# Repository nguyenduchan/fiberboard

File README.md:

# Fiberboard

Fiberboard là bo mạch điều khiển **logic tích hợp (AIO)**, không có driver stepper Nema. Dùng cho bơm DC, cấp liệu feeder, báo vật thể lạ và mini filler.

Trên bo có **đế cắm ESP32-DevKitC** (nạp phần mềm nhúng qua USB trên module). Nguồn vào **9–24 VDC**. Hai kênh quang **sợi POF 1 mm** (AFBR) gắn trên PCB. Đầu ra relay và van solenoid, **RS485**. Mỗi giắc vào/ra có **đèn SMD 0805** sát cọc. Trong cột nguồn có đèn debug: **D27** sáng khi +24 V sau bảo vệ còn điện, **D25** khi buck ra +5 V, **D6** khi LDO ra 3,3 V. Không có header OLED trên bo.

Kho mã này chỉ chứa thiết kế KiCad và script sinh mạch/layout. **Phần mềm nhúng (firmware)** không có trong kho.

Ghi chú thiết kế chi tiết: [`pcb/DESIGN_NOTES.txt`](pcb/DESIGN_NOTES.txt)

Khối **bảo vệ 24 V + buck** (dùng chung nhiều loại bo): [`pcb/PWR_24V_PROTECT_BUCK_GUIDE.txt`](pcb/PWR_24V_PROTECT_BUCK_GUIDE.txt)

---

## Chức năng các khối

| Khối | Mô tả |
|------|--------|
| **MCU** | ESP32-DevKitC trên đế cắm; nạp firmware qua USB trên module |
| **Nguồn** | VIN → **F1/L2/RV1/D7/Q12/C4** → **XL1509** → **+5V**. Mỗi relay lấy +5 V qua ferrite riêng (FB4 / FB5). **AMS1117** → 3,3 V. Chỉ **một** cầu chì F1 tại nguồn tổng 24 V. Mass **NT1+D11+C23+FB3**. Chi tiết: [`pcb/PWR_24V_PROTECT_BUCK_GUIDE.txt`](pcb/PWR_24V_PROTECT_BUCK_GUIDE.txt) |
| **Quang 2 kênh** | Phát AFBR-1624Z + thu AFBR-2624Z mỗi kênh; sợi POF 1 mm cắm trên bo |
| **Đầu vào số** | FOOT (công tắc chân), NPN (cảm biến); cách ly quang PC817 |
| **Đầu ra** | 2 relay G6KU (COM/NO/NC) + 1 van solenoid (MOSFET 24 V); domino J5/J6/J7 (**2EDG5.08**, bước 5,08 mm); flyback D3/D4 (cuộn relay 5 V), D5 SS34 (solenoid trên J7); driver 2N3904 + AO3400A. Tiếp điểm relay kín — tải cảm lớn: snubber/diode tại tải hoặc theo catalog relay |
| **Giao tiếp** | RS485 bán song công (MAX485); **TVS D9/D10** + **R18/R19** trên A/B; LED trạng thái; I2C chỉ trên ESP32 |

Bảo vệ trên bo (tóm tắt): **F1** = đế cầu chì **5×20 mm có nắp** (chân 22,6 mm) tại nguồn tổng 24 V, ống sứ 4 A thay bằng tay, không PPTC SMD; **L2, RV1, D7, C4**; mass **NT1, D11, C23, FB3**; relay **D12/C24**; van lấy **+24V** sau F1. Đèn **Vào / Chì / 24V / 5V / 3V3** chỉ chỗ nguồn đứt. Đầu vào quang PC817; RS485 **D9/D10**. Lắp tủ: nguồn 24 V ≥ 1,5–2 A, dây xoắn, IEC 61000-6-2; dừng khẩn / SIL — phần cứng an toàn riêng.

---

## Đầu nối ra ngoài (I/O)

**Cạnh dài trên** (trái → phải): `J1 | J3 | J4 | F1T | F1R | F2T | F2R` — nguồn vào 24 V, chân, NPN, quang.

**Cạnh dài dưới** (trái → phải): `J5 | J6 | J7 | J2 | J8` — relay 1, relay 2, van, giắc 24 V ra cho bàn phím, rồi RS485. Các giắc giãn trên suốt cạnh; cột relay, van và RS485 rộng hơn để xếp linh kiện trong khung của cọc. Cột trái trong lòng là bảo vệ 24 V, cột kế là buck.

| Ref | Tên | Chân | Ý nghĩa |
|-----|-----|------|---------|
| **J1** | VIN | 1 | +9 … +24 VDC |
| | | 2 | Mass domino nguồn |
| **F1T** | Quang 1 phát | POF | Phát; cắm sợi 1 mm thẳng vào mắt hướng ra cạnh bo |
| **F1R** | Quang 1 thu | POF | Thu kênh 1 (cùng chiều cắm như phát) |
| **F2T** | Quang 2 phát | POF | Phát kênh 2 |
| **F2R** | Quang 2 thu | POF | Thu kênh 2 |
| **J3** | FOOT | 1 | Cực A công tắc chân (qua opto) |
| | | 2 | Cực K / mass về |
| **J4** | NPN | 1 | V+ 24 V cho cảm biến hiện trường |
| | | 2 | SIG (tín hiệu NPN) |
| | | 3 | Mass hiện trường (GND_PWR) |
| **J5** | RELAY 1 | 1 / 2 / 3 | COM / NO / NC |
| **J6** | RELAY 2 | 1 / 2 / 3 | COM / NO / NC |
| **J7** | SOLENOID | 1 | +24 V (cực dương cuộn van) |
| | | 2 | SOL− (cực âm; bo cắt mass phía âm) |
| **J2** | Keyboard | 1 / 2 | +24 V đã qua F1 (cùng rail +24V) / mass nguồn. Cấp cho J_PWR mạch keyboard |
| **J8** | RS485 | 1 / 2 / 3 | A / B / mass logic (**2EDG5.08-3P** cái trên bo) |

### Domino hiện trường — **2EDG5.08** (dễ mua Shopee)

| Hạng mục | Khuyến nghị |
|----------|-------------|
| **Trên PCB** | Socket **2EDG5.08** cái, chân ngang 5,08 mm (footprint `Fiberboard:Terminal_2EDG5.08-…`) |
| **Dây ra hiện trường** | **Đầu đực 2EDG** cùng bước (bộ **đực + cái** 2P/3P), siết dây vào đực; hoặc cáp **CH5.08** một đầu + đầu đực 2EDG tùy shop |
| **Tìm mua** | Shopee: `2EDG5.08 3P đực cái thẳng` · `2EDG5.08 2P` · `cáp CH5.08 3P 20cm` (đầu jack — thường gắn thêm đực 2EDG nếu cần) |

### RS485 (J8)

| Hạng mục | Khuyến nghị |
|----------|-------------|
| **Cắm** | **2EDG5.08-3P** đực (giống J4–J6) |
| **Cáp** | Đôi xoắn **2×0,25–0,5 mm²** + bọc chắn; **A/B** chân 1–2, **mass** chân 3; bọc chắn nối mass **một đầu** |
| **Trên bo** | **R15 100 Ω** giữa A–B (điểm cuối bus — termination; gộp mã với R13) |
| **Bố trí** | **J8** ở **cạnh dài dưới** (cùng hàng relay/van), góc phải |

| Ref | Socket trên bo | Dây hiện trường (phổ biến VN) |
|-----|----------------|-------------------------------|
| **J1, J3, J7** | 2EDG **2P** cái | Đực **2EDG5.08-2P** + dây 0,5–1,5 mm² |
| **J4, J5, J6, J8** | 2EDG **3P** cái | Đực **2EDG5.08-3P** (+ cáp xoắn có bọc cho RS485) |

Cột I/O tính theo **bề ngang cắm đực 2EDG**, xếp trên **cạnh dài** của hộp 145×90×40.

---

## GPIO ESP32 (tham chiếu firmware)

Tên tín hiệu trong firmware giữ nguyên; cột **Hướng** = vào/ra MCU.

| GPIO | Tín hiệu | Hướng | Ghi chú |
|------|-----------|-------|---------|
| IO32 | FIBER1_PWM | Ra | LEDC PWM → phát quang kênh 1 |
| IO33 | FIBER2_PWM | Ra | LEDC PWM → phát quang kênh 2 |
| IO4 | FIBER1_DIG | Vào | TTL từ thu quang kênh 1 |
| IO15 | FIBER2_DIG | Vào | TTL từ thu quang kênh 2 |
| IO25 | IN_FOOT | Vào | Công tắc chân (sau opto) |
| IO26 | IN_NPN | Vào | Cảm biến NPN (sau opto) |
| IO27 | OUT_RLY1 | Ra | Driver relay 1 |
| IO14 | OUT_RLY2 | Ra | Driver relay 2 |
| IO13 | OUT_MOS | Ra | Solenoid |
| IO16 | RS485_RX | Vào | UART RX (MAX485) |
| IO17 | RS485_DE | Ra | DE và RE# (MAX485) |
| IO23 | RS485_TX | Ra | UART TX |
| IO21 | I2C_SDA | Hai chiều | Không ra header bo (tùy chọn ngoài) |
| IO22 | I2C_SCL | Ra | Không ra header bo (tùy chọn ngoài) |

IO32, IO33, IO4, IO15, IO23 và IO16 có điện trở nối tiếp 1 kΩ (R40–R45) trước mắt quang và MAX485.

---

## Thư mục trong kho mã

| Đường dẫn | Vai trò |
|-----------|---------|
| `pcb/fiberboard-logic.kicad_pro` | Dự án KiCad 10 (sơ đồ + PCB) |
| `pcb/DESIGN_NOTES.txt` | Ghi chú nguồn, layout, quang |
| `pcb/PWR_24V_PROTECT_BUCK_GUIDE.txt` | Hướng dẫn khối bảo vệ 24 V và buck (dùng chung) |
| `pcb/BOM.txt` | BOM đầy đủ + bảng **gộp mã** linh kiện cơ bản + giá VND |
| `pcb/ASSEMBLY.txt` | Vùng lắp ráp tùy chọn theo giắc (DNP cả nhóm) |
| `pcb/libraries/` | Symbol và footprint Fiberboard |
| `pcb/scripts/generate_kicad_project.py` | Sinh lại sơ đồ/PCB/thư viện |
| `pcb/scripts/connectivity.py` | Danh sách mạng và kết nối |
| `pcb/scripts/pcb_layout.py` | Vị trí footprint, silk I/O |
| `pcb/scripts/check_pcb_layout.py` | Kiểm tra chồng linh kiện sau khi sinh PCB |
| `pcb/scripts/autoroute.py` | Đi dây tự động (A* trên lưới 0,1 mm, 2 lớp; lõi tăng tốc bằng numba trong `maze_nb.py`): mọi chân ra thẳng ≥0,6 mm rồi mới rẽ; đi dây cả GND/GND_PWR; chân kẹt thì dịch nhẹ linh kiện thụ động (bước 0,25 mm, ≤3 mm, không tạo chồng courtyard mới) và rip-up net chắn đường. Chạy sau `generate_kicad_project.py`: `python pcb/scripts/autoroute.py --passes 7 --png route.png` (~5–6 phút) |

---

## Cách làm việc

| Bước | Việc cần làm |
|------|----------------|
| 1 | Mở `pcb/fiberboard-logic.kicad_pro` trong KiCad 10 |
| 2 | Sau khi sửa Python: `python pcb/scripts/generate_kicad_project.py` (cần KiCad 10; đường dẫn KiCad trong script) |
| 3 | Đi dây PCB theo ratsnest; refill pour **GND** và **GND_PWR** tại điểm sao **NT1** (cạnh C4) |
| 3b | Sau `generate_kicad_project.py`: `python pcb/scripts/check_pcb_layout.py` — kiểm tra chồng linh kiện. **DRC đỏ “unconnected”** là bình thường khi chưa đi dây (file sinh ra không có track) |

---

## Kích thước bo và vỏ

> **Vỏ:** hộp PLC **145 × 90 × 40 mm** (mã 145T-1D). Giắc nhà máy nằm trên **cạnh dài** (~20 vị trí, pitch 5 mm), không phải hai đầu 90 mm. Lòng thân khoảng **125 × 90 mm**. PCB **118 × 84 mm**.

| Hạng mục | Giá trị |
|----------|---------|
| **PCB** | 118 × 84 mm |
| **Vỏ** | Hộp PLC ABS 145 × 90 × 40 mm |
| **Giắc** | Cạnh dài trên: J1 nguồn vào, J3 chân, J4 NPN, quang. Cạnh dài dưới: J5/J6 relay, J7 van sát J2 (24 V ra bàn phím), J8 RS485 |
| **Lớp / độ dày** | 2 lớp FR4, 1,6 mm |
| **Lắp ráp** | SMD ưu tiên; domino và AFBR xuyên lỗ theo footprint |
| **Silk mép dưới** | Cột I/O: nhãn tiếng Việt sát giắc cắm, căn giữa ô; chỉnh trong `pcb/scripts/pcb_layout.py` → `IO_LABELS` |

### Ước giá linh kiện (tham chiếu)

Chi tiết từng mã: [`pcb/BOM.txt`](pcb/BOM.txt). Tóm tắt (lẻ VN, 1 bo):

| Hạng mục | Khoảng (k VND) |
|----------|----------------|
| Linh kiện trên PCB (không gồm module ESP32) | ~530 – 1.060 |
| ESP32-DevKitC | ~90 – 185 |
| PCB 2 lớp 118×84 mm | ~25 – 120 |
| **Lắp đủ một máy** | **~645 – 1.365** |

Khối nguồn + cầu chì 5×20: ~165–300k (không relay). Quang AFBR và relay là hai khoản biến động lớn nhất.

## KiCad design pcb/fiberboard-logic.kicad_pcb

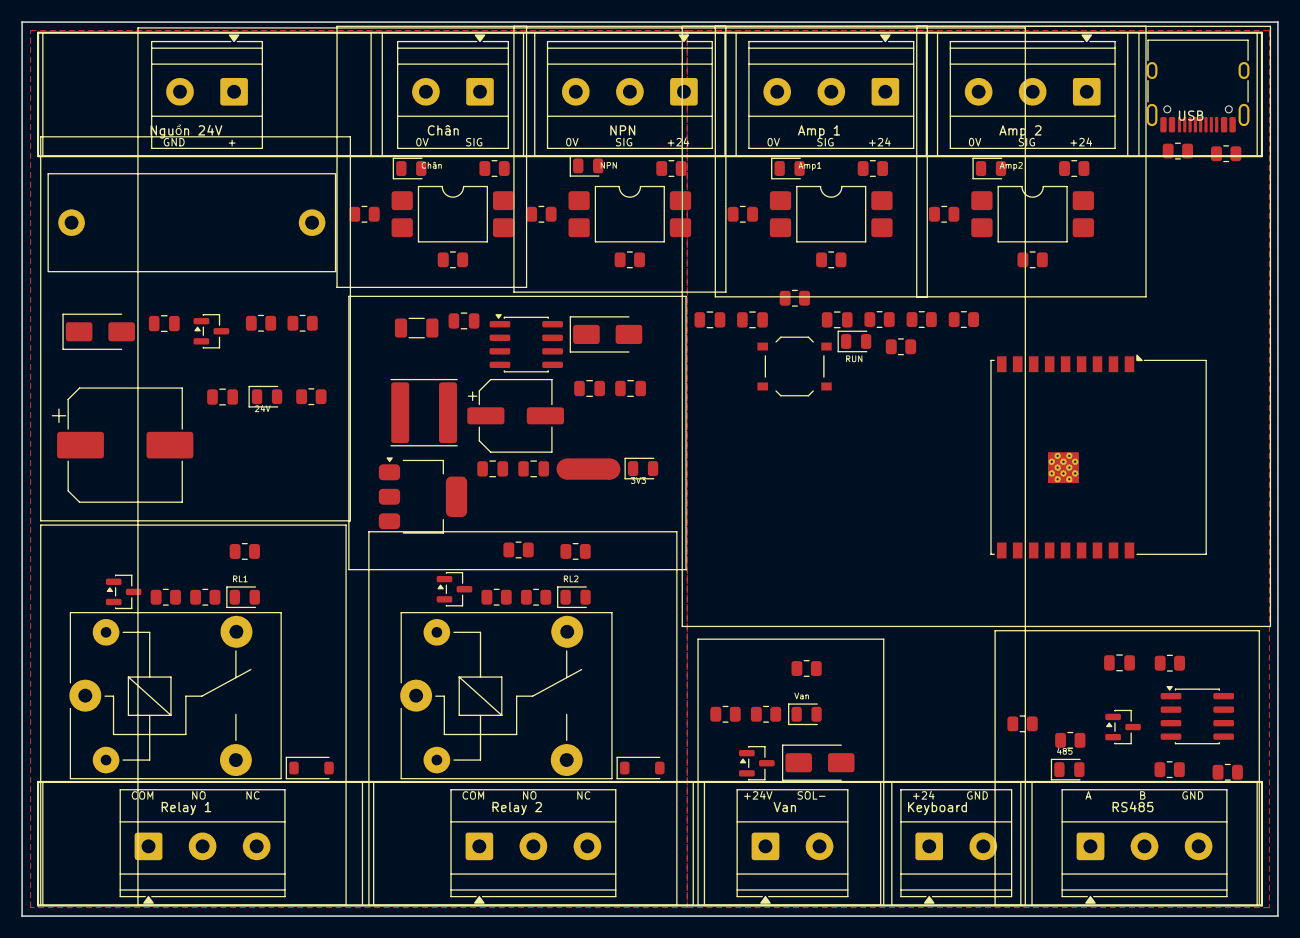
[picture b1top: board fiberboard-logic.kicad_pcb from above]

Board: 2 copper layers, 118.0 x 84.0 mm, 97 parts (0 on the bottom side), 62 nets, no tracks yet.

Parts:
C2: 220uF 10V; CP_Elec_6.3x5.4
C3: 22uF; C_0805_2012Metric
C4: 470uF 35V; CP_Elec_10x10.5
C5, C9, C11, C18: 100nF; C_0805_2012Metric
C7, C8: 10uF; C_0805_2012Metric
C10: 1uF; C_0805_2012Metric
C14, C15, C17: 100nF 50V; C_0805_2012Metric
C16: 10uF 50V; C_1206_3216Metric
D3, D4: 1N4148W; D_SOD-123
D5, D8: SS34; D_SMA
D6: 3V3; LED_0805_2012Metric
D7: SMAJ26A; D_SMA
D9: PSM712; SOT-23
D15: FOOT; LED_0805_2012Metric
D16: NPN; LED_0805_2012Metric
D17: RLY1; LED_0805_2012Metric
D18: RLY2; LED_0805_2012Metric
D19: VAN; LED_0805_2012Metric
D20: 485; LED_0805_2012Metric
D27: 24V; LED_0805_2012Metric
D30: RUN; LED_0805_2012Metric
D31: AMP1; LED_0805_2012Metric
D32: AMP2; LED_0805_2012Metric
F1: 5x20 su 4A; Fuseholder_5x20mm_Covered
J1: VIN; Terminal_2EDG5.08-1x02_P5.08mm_Horizontal
J2: KB24; Terminal_2EDG5.08-1x02_P5.08mm_Horizontal
J3: FOOT; Terminal_2EDG5.08-1x02_P5.08mm_Horizontal
J4: NPN; Terminal_2EDG5.08-1x03_P5.08mm_Horizontal
J5: RLY1; Terminal_2EDG5.08-1x03_P5.08mm_Horizontal
J6: RLY2; Terminal_2EDG5.08-1x03_P5.08mm_Horizontal
J7: SOL; Terminal_2EDG5.08-1x02_P5.08mm_Horizontal
J8: RS485; Terminal_2EDG5.08-1x03_P5.08mm_Horizontal
J9: AMP1; Terminal_2EDG5.08-1x03_P5.08mm_Horizontal
J10: AMP2; Terminal_2EDG5.08-1x03_P5.08mm_Horizontal
J11: USB-C; USB_C_Receptacle_HRO_TYPE-C-31-M-12
K1, K2: HF3FF-024-1ZS; Relay_SPDT_SANYOU_SRD_Series_Form_C
L1: 47uH 6045; L_Sunlord_SWPA6045S
NT1: GND_STAR; NetTie-2_SMD_Pad2.0mm
Q3, Q4: MMBT3904; SOT-23
Q5: AO3400A; SOT-23
Q12: AO3401A; SOT-23
R7, R8, R9, R10, R14, R26, R27, R28, R39, R47, R48, R49, R52, R53, R54, R55, R57, R58, R60, R61, R63: 10k; R_0805_2012Metric
R11, R12, R16, R24, R25, R29, R56, R59, R62: 1k; R_0805_2012Metric
R13, R18, R19: 10R; R_0805_2012Metric
R15: 120R; R_0805_2012Metric
R17: 27k; R_0805_2012Metric
R50, R51: 5.1k; R_0805_2012Metric
SW1: BOOT; SW_Push_1P1T_XKB_TS-1187A
U1: ESP32-C3-WROOM-02
U2: XL1509-5.0; SOIC-8_3.9x4.9mm_P1.27mm
U3: AMS1117-3.3; SOT-223-3_TabPin2
U5, U6, U9, U10: LTV-817S; SMDIP-4_W9.53mm
U7: SP3485EN; SOIC-8_3.9x4.9mm_P1.27mm

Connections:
+3V3: C3.1, C8.1, C9.1, C11.1, C18.1, R9.1, R10.1, R16.1, R24.1, R25.1, R52.1, R53.1, R54.1, R55.1, R56.1, R58.1, R59.1, R61.1, R62.1, U1.1, U3.2, U7.8
+5V: C2.1, C5.1, C7.1, L1.2, U2.3, U3.3
+24V: C4.1, C14.1, C16.1, C17.1, D3.1, D4.1, D5.1, J2.1, J4.1, J7.1, J9.1, J10.1, K1.5, K2.5, Q12.2, R7.1, R8.1, R26.1, R27.1, R28.1, R39.1, R57.1, R60.1, R63.1, U2.1
AMP1_AN: R57.2, U9.1
AMP1_SIG: J9.2, U9.2
AMP2_AN: R60.2, U10.1
AMP2_SIG: J10.2, U10.2
BUCK_SW: D8.1, L1.1, U2.2
ESP_BOOT: R55.2, SW1.1, U1.8
ESP_EN: C10.1, R52.2, U1.2
ESP_IO2: R53.2, U1.16
FET_G: Q12.1, R17.1, R63.2
FOOT_AN: R7.2, U5.1
FOOT_SIG: J3.1, U5.2
GND: C3.2, C7.2, C8.2, C9.2, C10.2, C11.2, C18.2, D6.1, D9.3, D20.1, J8.3, J11.A1, J11.A12, J11.B1, J11.B12, J11.SH, NT1.2, R49.2, R50.2, R51.2, SW1.2, U1.9, U1.19, U3.1, U5.3, U6.3, U7.5, U9.3, U10.3
GND_PWR: C2.2, C4.2, C5.2, C14.2, C15.2, C16.2, C17.2, D7.2, D8.2, D27.1, J1.2, J2.2, J3.2, J4.3, J9.3, J10.3, NT1.1, Q3.2, Q4.2, Q5.2, R14.2, R17.2, R47.2, R48.2, U2.4, U2.5, U2.6, U2.7, U2.8
IN_AMP1: D31.1, R58.2, U1.5, U9.4
IN_AMP2: D32.1, R61.2, U1.6, U10.4
IN_FOOT: D15.1, R9.2, U1.3, U5.4
IN_NPN: D16.1, R10.2, U1.4, U6.4
J3_AN: D15.2, R24.2
J4_AN: D16.2, R25.2
J5_AN: D17.2, R26.2
J6_AN: D18.2, R27.2
J7_AN: D19.2, R28.2
J8_AN: D20.2, R29.2
J9_AN: D31.2, R59.2
J10_AN: D32.2, R62.2
LED_RUN: D30.1, R54.2, U1.7
MOS_G: Q5.1, R13.2, R14.1
NPN_AN: R8.2, U6.1
NPN_SIG: J4.2, U6.2
OUT_MOS: R13.1, U1.10
OUT_RLY1: R11.1, U1.18
OUT_RLY2: R12.1, U1.17
P3V3_AN: D6.2, R16.2
P24_AN: D27.2, R39.2
RLY1_B: Q3.1, R11.2, R47.1
RLY1_COIL: D3.2, D17.1, K1.2, Q3.3
RLY1_COM: J5.1, K1.1
RLY1_NC: J5.3, K1.4
RLY1_NO: J5.2, K1.3
RLY2_B: Q4.1, R12.2, R48.1
RLY2_COIL: D4.2, D18.1, K2.2, Q4.3
RLY2_COM: J6.1, K2.1
RLY2_NC: J6.3, K2.4
RLY2_NO: J6.2, K2.3
RS485_A: R18.1, U7.6
RS485_A_BUS: D9.1, J8.1, R15.1, R18.2
RS485_B: R19.1, U7.7
RS485_B_BUS: D9.2, J8.2, R15.2, R19.2
RS485_DE: R29.1, R49.1, U1.15, U7.2, U7.3
RS485_RX: U1.11, U7.1
RS485_TX: U1.12, U7.4
RUN_AN: D30.2, R56.2
SOL_LO: D5.2, D19.1, J7.2, Q5.3
USB_CC1: J11.A5, R50.1
USB_CC2: J11.B5, R51.1
USB_DN: J11.A7, J11.B7, U1.13
USB_DP: J11.A6, J11.B6, U1.14
VIN_FUSE: C15.1, D7.1, F1.2, Q12.3
VIN_RAW: F1.1, J1.1
